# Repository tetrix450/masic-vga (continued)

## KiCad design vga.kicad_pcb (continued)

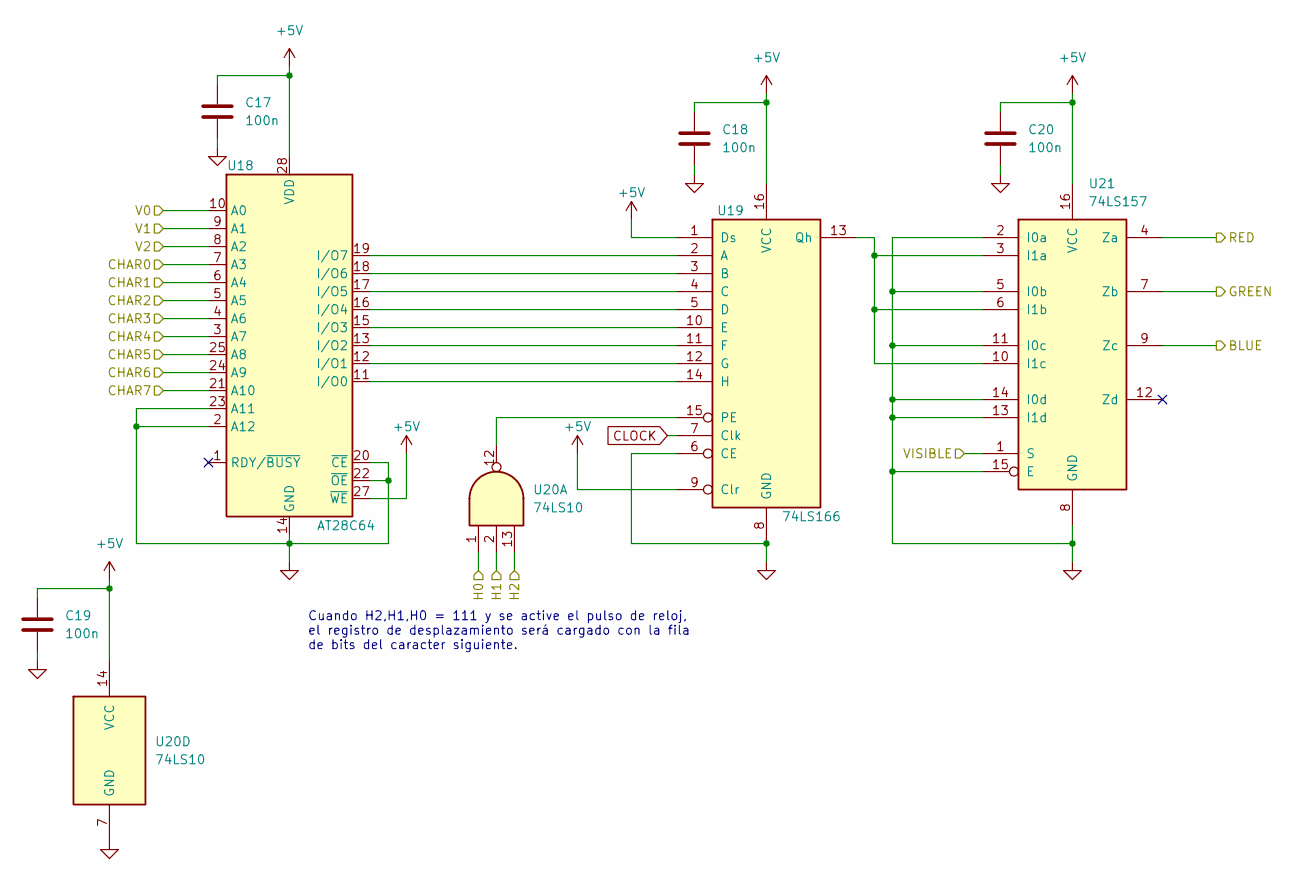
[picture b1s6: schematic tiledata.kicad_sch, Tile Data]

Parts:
C17, C18, C19, C20: 100n; C_Disc_7.62mm
U18: AT28C64; DIP-28_W15.24mm
U19: 74LS166; DIP-16_W7.62mm
U20: 74LS10; DIP-14_W7.62mm
U21: 74LS157; DIP-16_W7.62mm

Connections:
+5V: C17.1, C18.1, C19.1, C20.1, U18.27 (~WE), U18.28 (VDD), U19.1 (Ds), U19.9 (Clr), U19.16 (VCC), U20.14 (VCC), U21.16 (VCC); also elsewhere on the board
/Delay de 8 ciclos/VISIBLE_OUT: U21.1 (S); also elsewhere on the board
/Tile Data (EEPROM)/BLUE: U21.9 (Zc); also elsewhere on the board
/Tile Data (EEPROM)/CHAR0: U18.7 (A3); also elsewhere on the board
/Tile Data (EEPROM)/CHAR1: U18.6 (A4); also elsewhere on the board
/Tile Data (EEPROM)/CHAR2: U18.5 (A5); also elsewhere on the board
/Tile Data (EEPROM)/CHAR3: U18.4 (A6); also elsewhere on the board
/Tile Data (EEPROM)/CHAR4: U18.3 (A7); also elsewhere on the board
/Tile Data (EEPROM)/CHAR5: U18.25 (A8); also elsewhere on the board
/Tile Data (EEPROM)/CHAR6: U18.24 (A9); also elsewhere on the board
/Tile Data (EEPROM)/CHAR7: U18.21 (A10); also elsewhere on the board
/Tile Data (EEPROM)/GREEN: U21.7 (Zb); also elsewhere on the board
/Tile Data (EEPROM)/H0: U20.1; also elsewhere on the board
/Tile Data (EEPROM)/H1: U20.2; also elsewhere on the board
/Tile Data (EEPROM)/H2: U20.13; also elsewhere on the board
/Tile Data (EEPROM)/RED: U21.4 (Za); also elsewhere on the board
/Tile Data (EEPROM)/V0: U18.10 (A0); also elsewhere on the board
/Tile Data (EEPROM)/V1: U18.9 (A1); also elsewhere on the board
/Tile Data (EEPROM)/V2: U18.8 (A2); also elsewhere on the board
CLOCK: U19.7 (Clk); also elsewhere on the board
GND: C17.2, C18.2, C19.2, C20.2, U18.2 (A12), U18.14 (GND), U18.20 (~CE), U18.22 (~OE), U18.23 (A11), U19.6 (CE), U19.8 (GND), U20.7 (GND), U21.2 (I0a), U21.5 (I0b), U21.8 (GND), U21.11 (I0c), U21.13 (I1d), U21.14 (I0d), U21.15 (E); also elsewhere on the board
unnamed: U18.11 (I/O0), U19.14 (H)
unnamed: U18.12 (I/O1), U19.12 (G)
unnamed: U18.13 (I/O2), U19.11 (F)
unnamed: U18.15 (I/O3), U19.10 (E)
unnamed: U18.16 (I/O4), U19.5 (D)
unnamed: U18.17 (I/O5), U19.4 (C)
unnamed: U18.18 (I/O6), U19.3 (B)
unnamed: U18.19 (I/O7), U19.2 (A)
unnamed: U19.15 (PE), U20.12
unnamed: U19.13 (Qh), U21.3 (I1a), U21.6 (I1b), U21.10 (I1c)

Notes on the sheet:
Cuando H2,H1,H0 = 111 y se active el pulso de reloj, el registro de desplazamiento será cargado con la fila de bits del caracter siguiente.

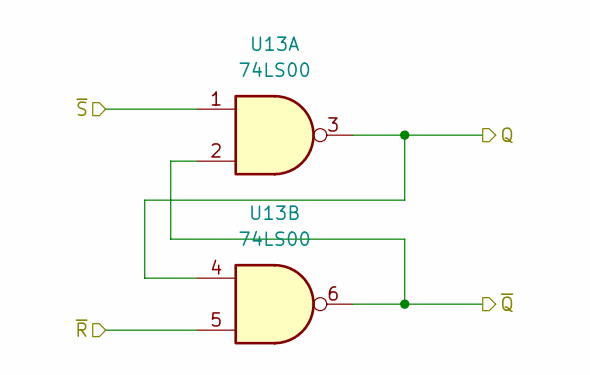
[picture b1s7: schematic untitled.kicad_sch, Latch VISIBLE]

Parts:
U13: 74LS00; DIP-14_W7.62mm

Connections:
/Generador de señales/VBLANK LATCH/Q: U13.3, U13.4; also elsewhere on the board
/Generador de señales/VBLANK LATCH/~Q: U13.2, U13.6
/Generador de señales/VBLANK LATCH/~R: U13.5; also elsewhere on the board
/Generador de señales/VBLANK LATCH/~S: U13.1; also elsewhere on the board
/Generador de señales/VSYNC_LATCH/Q: U13.8, U13.12; also elsewhere on the board
/Generador de señales/VSYNC_LATCH/~Q: U13.10, U13.11; also elsewhere on the board
/Generador de señales/VSYNC_LATCH/~R: U13.13; also elsewhere on the board
/Generador de señales/VSYNC_LATCH/~S: U13.9; also elsewhere on the board

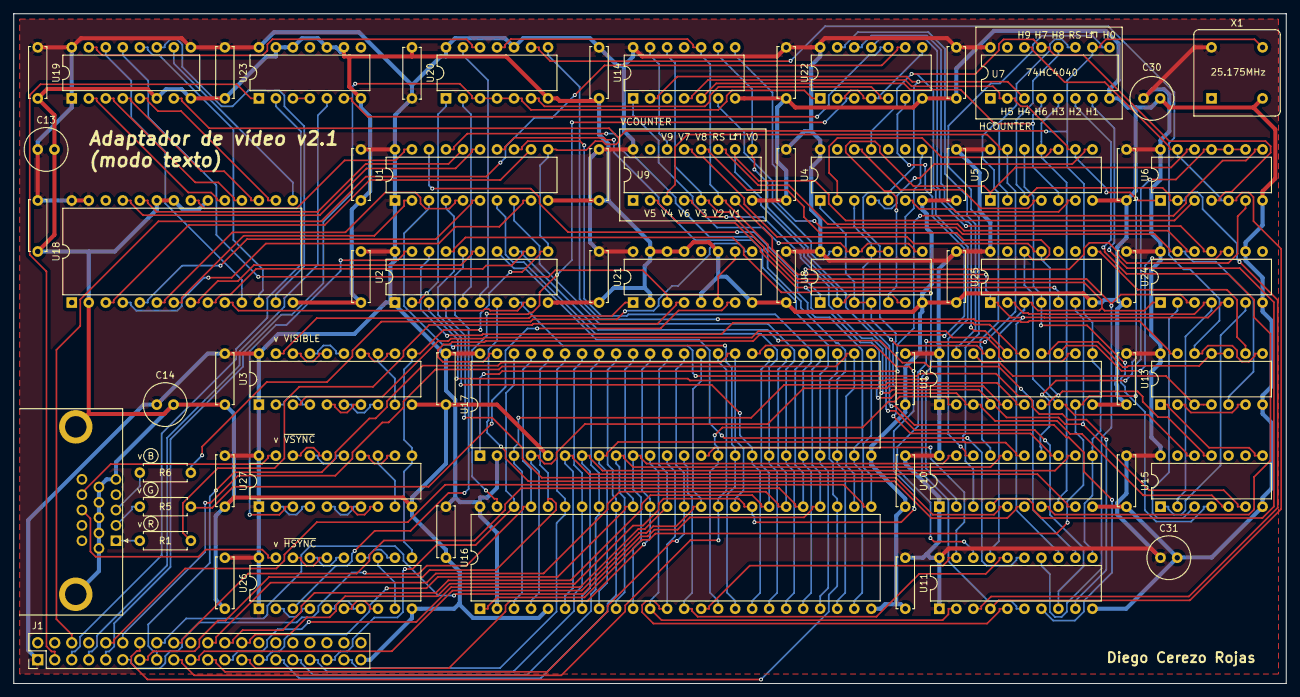
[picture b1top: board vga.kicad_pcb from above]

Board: 2 copper layers, 190.0 x 100.0 mm, 64 parts (1 on the bottom side), 173 nets.
